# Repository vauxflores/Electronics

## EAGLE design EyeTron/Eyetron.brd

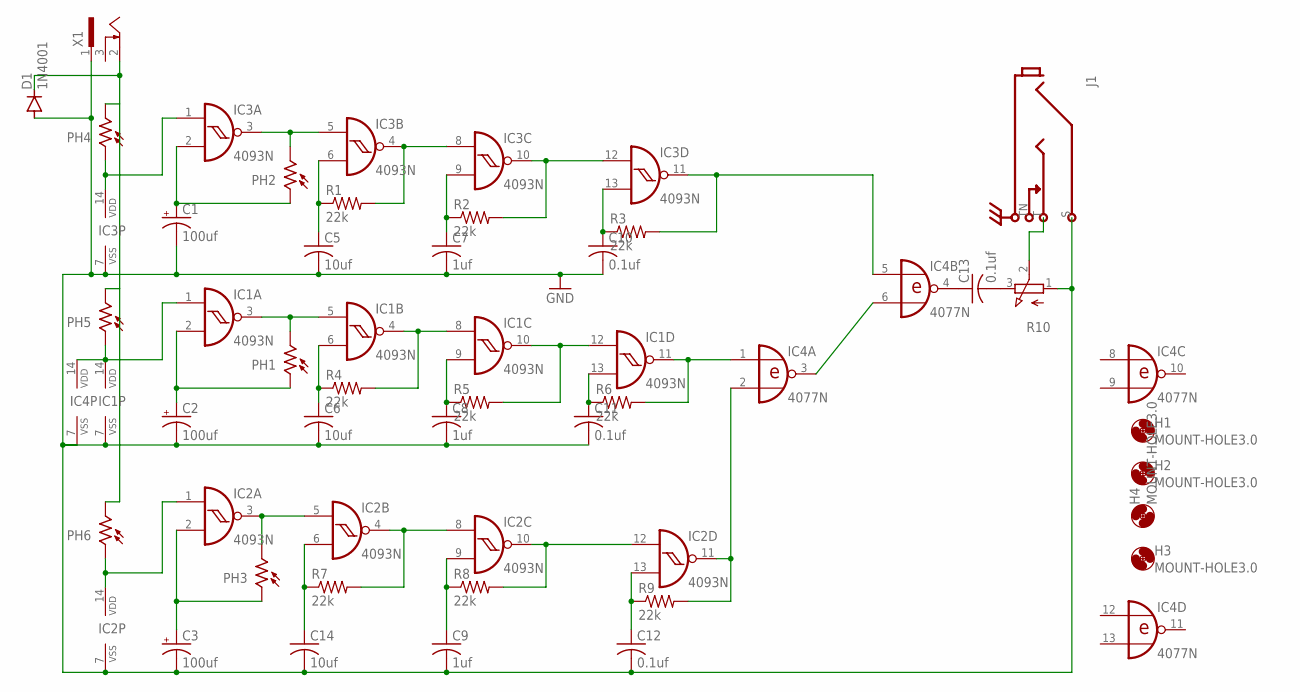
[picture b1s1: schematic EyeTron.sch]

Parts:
C1, C2, C3: 100uf; E2,5-6E
C5, C6, C14: 10uf; C050-025X075
C7, C8, C9: 1uf; C050-025X075
C10, C11, C12, C13: 0.1uf; C050-025X075
D1: 1N4001; DO41-10
H1, H2, H3, H4: MOUNT-HOLE3.0; 3,0
IC1, IC2, IC3: 4093N; DIL14
IC4: 4077N; DIL14
J1: MONOSW1GND; NEUTRIK-NRJ4HM-1
PH1, PH2, PH3, PH4, PH5, PH6: VT90N1; VT900
R1, R2, R3, R4, R5, R6, R7, R8, R9: 22k; 0207/7
R10: EVUF2L; EVUFXL
X1: SCD-014A; SCD-014-A

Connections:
GND: C1.-, C2.-, C3.-, C5.2, C6.2, C7.2, C8.2, C9.2, C10.2, C11.2, C12.2, C14.2, D1.A, IC1.7 (VSS), IC2.7 (VSS), IC3.7 (VSS), IC4.7 (VSS), J1.S, R10.1 (A), X1.1
unnamed: IC1.11 (O), IC4.1 (I0), R6.2
unnamed: IC1.10 (O), IC1.12 (I0), R5.2
unnamed: IC1.4 (O), IC1.8 (I0), R4.2
unnamed: IC1.3 (O), IC1.5 (I0), PH1.2
unnamed: IC2.3 (O), IC2.5 (I0), PH3.2
unnamed: IC2.4 (O), IC2.8 (I0), R7.2
unnamed: IC2.10 (O), IC2.12 (I0), R8.2
unnamed: IC2.11 (O), IC4.2 (I1), R9.2
unnamed: IC4.3 (O), IC4.6 (I1)
unnamed: IC3.3 (O), IC3.5 (I0), PH2.2
unnamed: IC3.4 (O), IC3.8 (I0), R1.2
unnamed: IC3.10 (O), IC3.12 (I0), R2.2
unnamed: IC3.11 (O), IC4.5 (I0), R3.2
unnamed: C1.+, IC3.2 (I1), PH2.1
unnamed: C2.+, IC1.2 (I1), PH1.1
unnamed: C3.+, IC2.2 (I1), PH3.1
unnamed: C5.1, IC3.6 (I1), R1.1
unnamed: C7.1, IC3.9 (I1), R2.1
unnamed: IC3.1 (I0), IC3.14 (VDD), PH4.1
unnamed: C10.1, IC3.13 (I1), R3.1
unnamed: IC1.1 (I0), IC1.14 (VDD), IC4.14 (VDD), PH5.1
unnamed: C6.1, IC1.6 (I1), R4.1
unnamed: C8.1, IC1.9 (I1), R5.1
unnamed: C11.1, IC1.13 (I1), R6.1
unnamed: C14.1, IC2.6 (I1), R7.1
unnamed: C9.1, IC2.9 (I1), R8.1
unnamed: C12.1, IC2.13 (I1), R9.1
unnamed: IC2.1 (I0), IC2.14 (VDD), PH6.1
unnamed: D1.C, PH4.2, PH5.2, PH6.2, X1.2
unnamed: C13.1, IC4.4 (O)
unnamed: C13.2, R10.3 (E)
unnamed: J1.T, R10.2 (S)

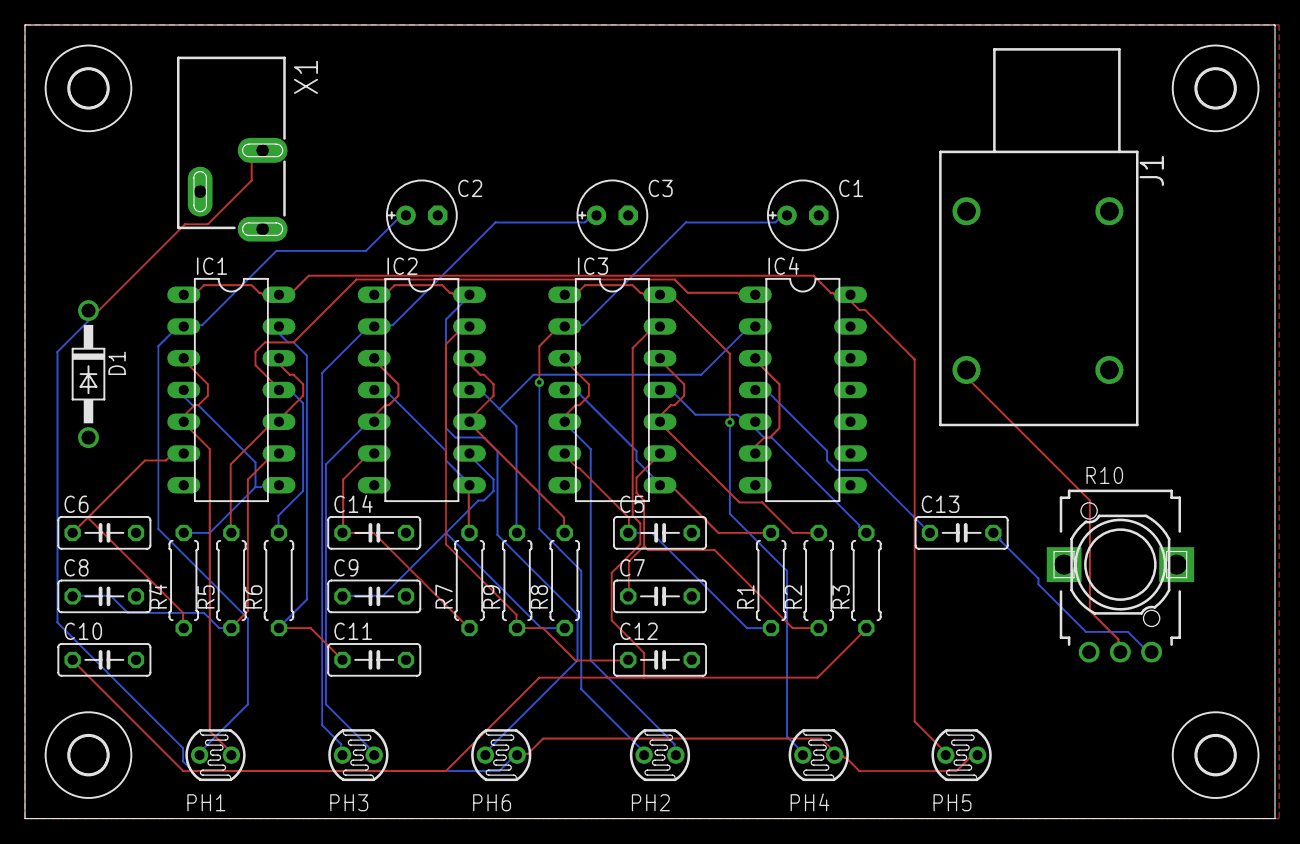
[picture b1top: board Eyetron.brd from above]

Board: 2 copper layers, 100.0 x 63.5 mm, 40 parts (0 on the bottom side), 33 nets.

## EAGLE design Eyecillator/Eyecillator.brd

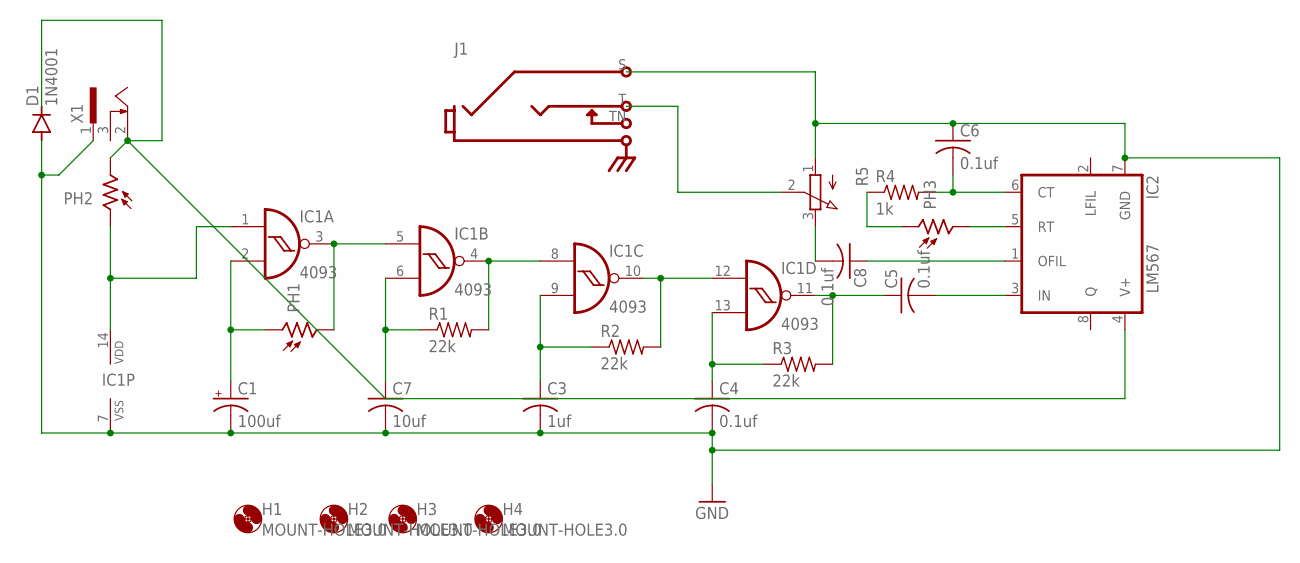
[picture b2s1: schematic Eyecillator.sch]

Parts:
C1: 100uf; E2,5-6E
C3: 1uf; C050-025X075
C4, C5, C6, C8: 0.1uf; C050-025X075
C7: 10uf; C050-025X075
D1: 1N4001; DO41-10
H1, H2, H3, H4: MOUNT-HOLE3.0; 3,0
IC1: 4093; DIL14
IC2: LM567; DIL08
J1: MONOSW1GND; NEUTRIK-NRJ4HM-1
PH1, PH2, PH3: VT90N1; VT900
R1, R2, R3: 22k; 0207/7
R4: 1k; 0207/7
R5: EVUF2L; EVUFXL
X1: SCD-014A; SCD-014-A

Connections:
GND: C1.-, C3.2, C4.2, C6.1, C7.2, D1.A, IC1.7 (VSS), IC2.7 (GND), J1.S, R5.1 (A), X1.1
unnamed: IC1.3 (O), IC1.5 (I0), PH1.2
unnamed: IC1.4 (O), IC1.8 (I0), R1.2
unnamed: IC1.10 (O), IC1.12 (I0), R2.2
unnamed: C1.+, IC1.2 (I1), PH1.1
unnamed: C7.1, IC1.6 (I1), R1.1
unnamed: C3.1, IC1.9 (I1), R2.1
unnamed: C4.1, IC1.13 (I1), R3.1
unnamed: C5.1, IC1.11 (O), R3.2
unnamed: IC1.1 (I0), IC1.14 (VDD), PH2.1
unnamed: C5.2, IC2.3 (IN)
unnamed: C6.2, IC2.6 (CT), R4.2
unnamed: IC2.5 (RT), PH3.2
unnamed: PH3.1, R4.1
unnamed: C8.1, IC2.1 (OFIL)
unnamed: C8.2, R5.3 (E)
unnamed: D1.C, IC2.4 (V+), PH2.2, X1.2
unnamed: J1.T, R5.2 (S)

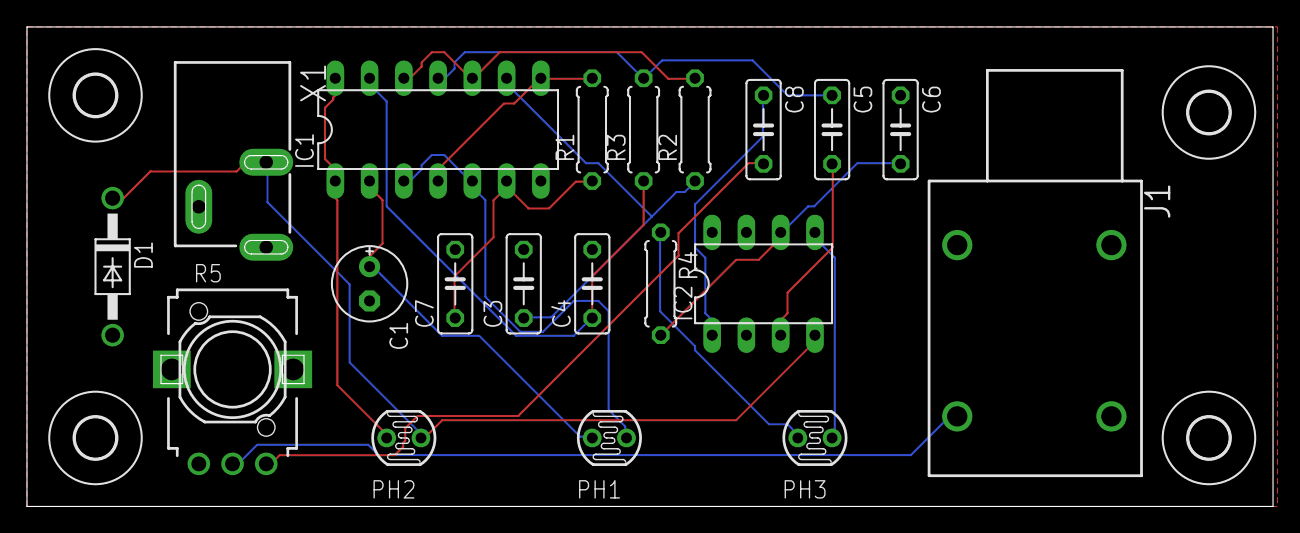
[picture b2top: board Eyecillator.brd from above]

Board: 2 copper layers, 92.4 x 35.5 mm, 24 parts (0 on the bottom side), 18 nets.

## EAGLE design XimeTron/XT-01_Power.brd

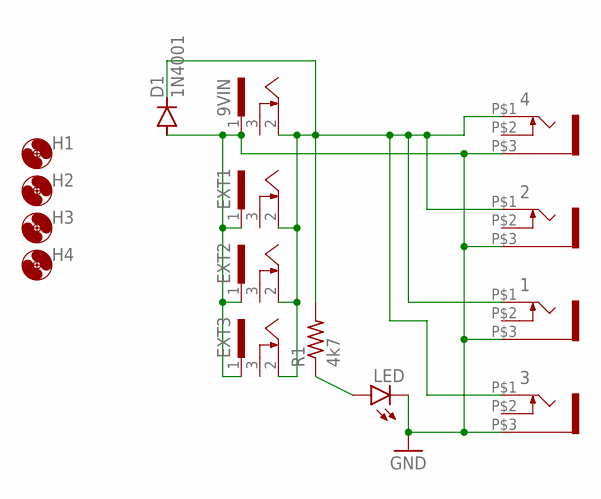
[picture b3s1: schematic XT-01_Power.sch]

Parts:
1, 2, 3, 4: WQP-PJ301M-12_JACK
9VIN: SCD-014A; SCD-014-A
D1: 1N4001; DO41-10
EXT1, EXT2, EXT3: SCD-014A; SCD-014-A
H1, H2, H3, H4: MOUNT-HOLE3.0; 3,0
LED: LED3MM
R1: 4k7; 0207/7

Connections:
GND: 1.P$3 (1), 2.P$3 (1), 3.P$3 (1), 4.P$3 (1), 9VIN.1, D1.A, EXT1.1, EXT2.1, EXT3.1, LED.K (C)
unnamed: LED.A, R1.1
unnamed: 1.P$1 (2), 2.P$1 (2), 3.P$1 (2), 4.P$1 (2), 9VIN.2, D1.C, EXT1.2, EXT2.2, EXT3.2, R1.2

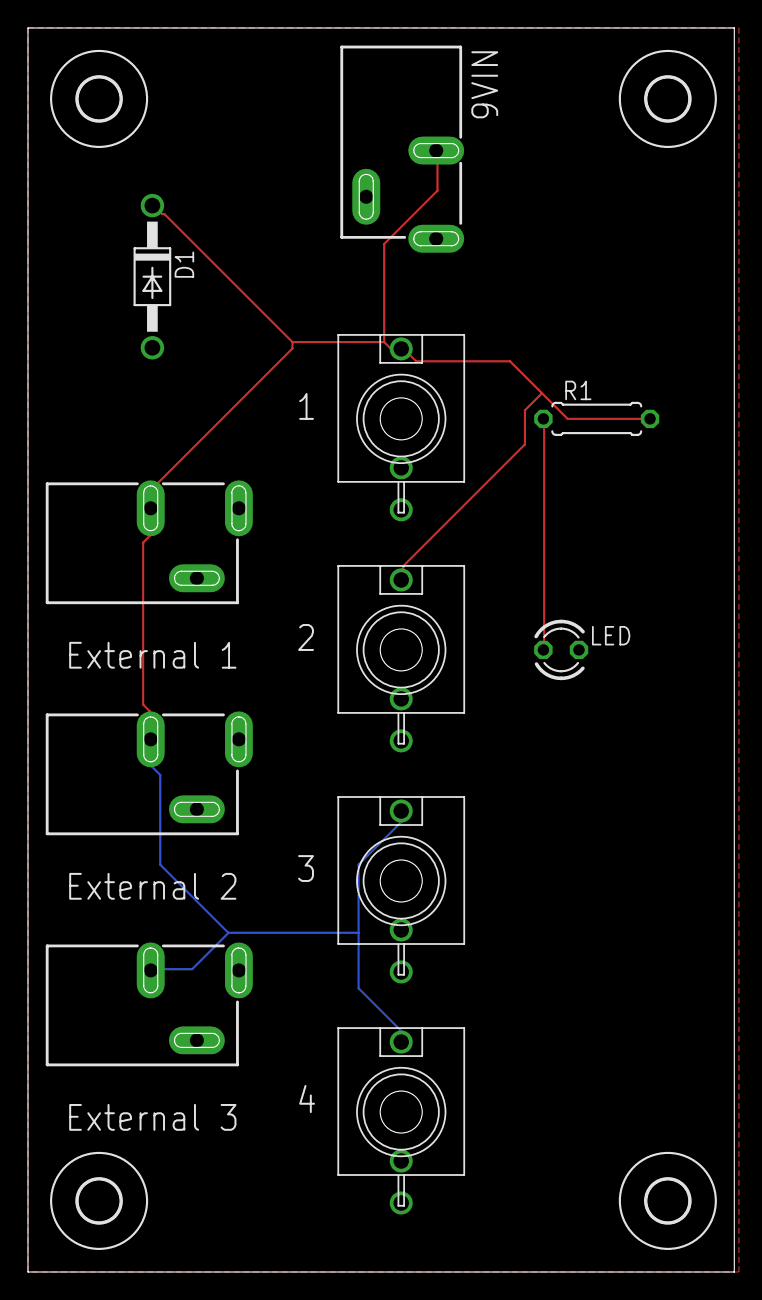
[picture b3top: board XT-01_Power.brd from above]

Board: 2 copper layers, 50.5 x 88.9 mm, 15 parts (0 on the bottom side), 3 nets.

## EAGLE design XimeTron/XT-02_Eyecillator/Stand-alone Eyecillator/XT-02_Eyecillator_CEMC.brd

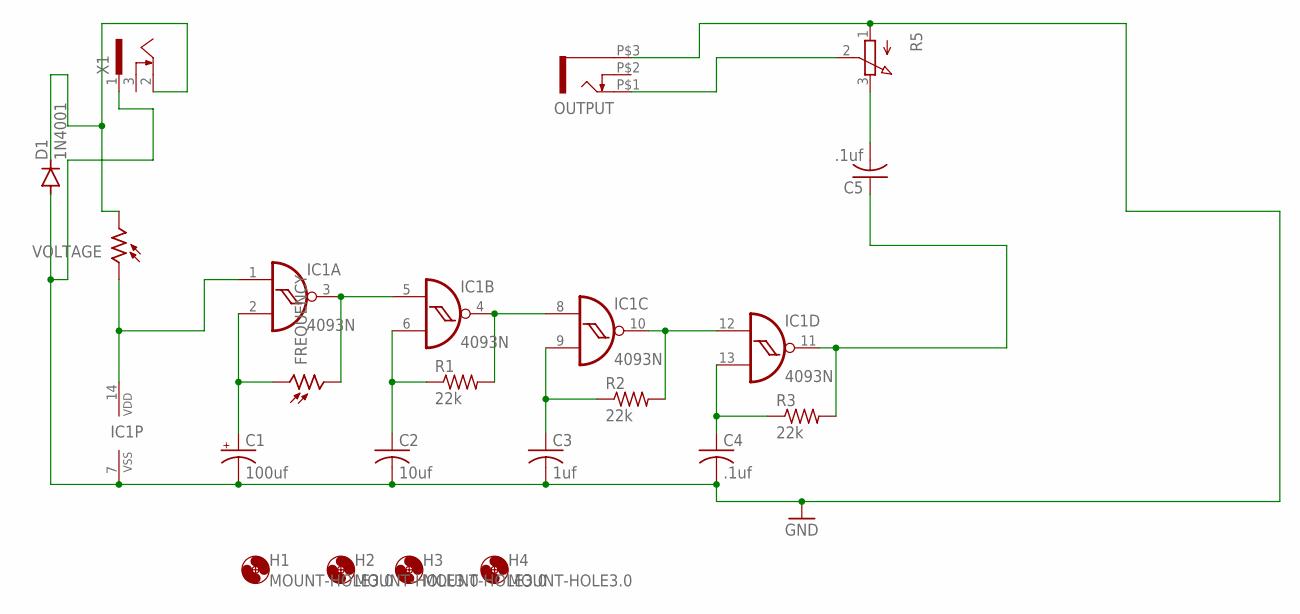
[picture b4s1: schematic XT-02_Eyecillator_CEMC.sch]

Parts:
C1: 100uf; E2,5-6E
C2: 10uf; C050-025X075
C3: 1uf; C050-025X075
C4, C5: .1uf; C050-025X075
D1: 1N4001; DO41-10
FREQUENCY: VT90N1; VT900
H1, H2, H3, H4: MOUNT-HOLE3.0; 3,0
IC1: 4093N; DIL14
OUTPUT: WQP-PJ301M-12_JACK
R1, R2, R3: 22k; 0207/7
R5: EVUF2L; EVUFXL
VOLTAGE: VT90N1; VT900
X1: SCD-014A; SCD-014-A

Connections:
GND: C1.-, C2.2, C3.2, C4.2, D1.A, IC1.7 (VSS), OUTPUT.P$3 (1), R5.1 (A), X1.1
unnamed: FREQUENCY.2, IC1.3 (O), IC1.5 (I0)
unnamed: IC1.4 (O), IC1.8 (I0), R1.2
unnamed: IC1.10 (O), IC1.12 (I0), R2.2
unnamed: C1.+, FREQUENCY.1, IC1.2 (I1)
unnamed: C2.1, IC1.6 (I1), R1.1
unnamed: C3.1, IC1.9 (I1), R2.1
unnamed: C4.1, IC1.13 (I1), R3.1
unnamed: C5.2, R5.3 (E)
unnamed: IC1.1 (I0), IC1.14 (VDD), VOLTAGE.1
unnamed: C5.1, IC1.11 (O), R3.2
unnamed: OUTPUT.P$1 (2), R5.2 (S)
unnamed: D1.C, VOLTAGE.2, X1.2

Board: 2 copper layers, 19 parts (0 on the bottom side), 13 nets, no tracks yet.

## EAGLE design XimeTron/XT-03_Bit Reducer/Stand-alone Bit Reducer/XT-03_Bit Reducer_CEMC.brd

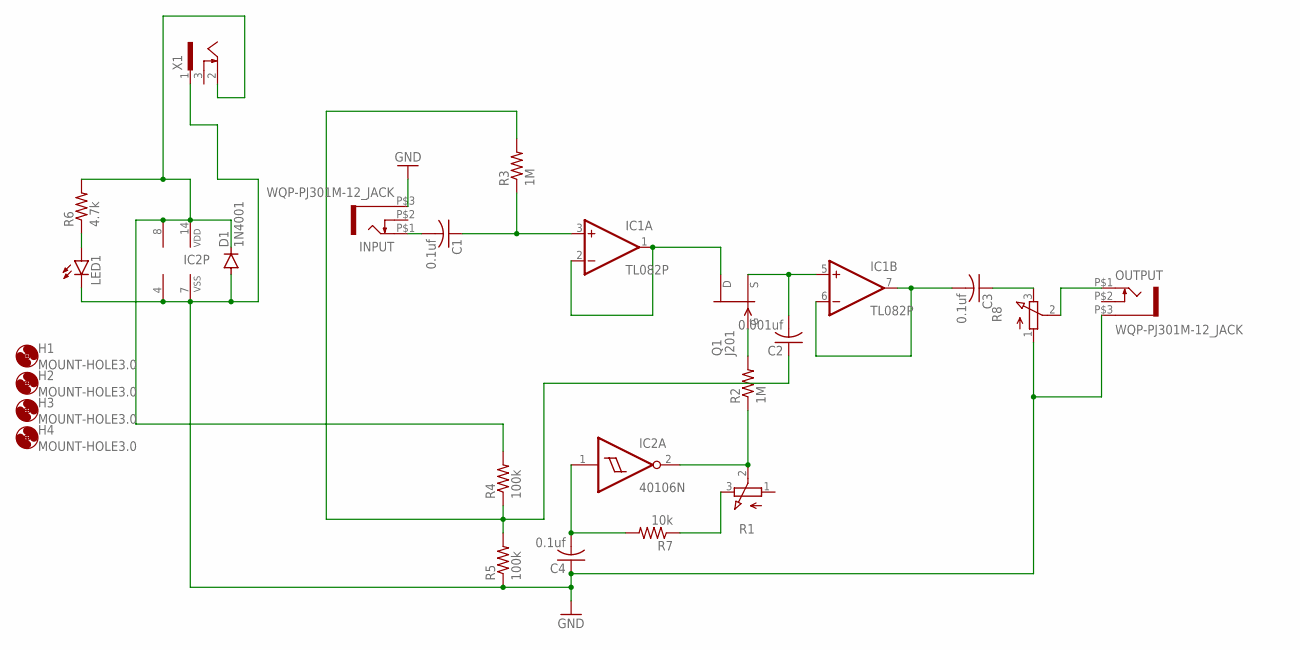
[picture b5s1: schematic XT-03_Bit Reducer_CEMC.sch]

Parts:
C1, C3, C4: 0.1uf; C050-025X075
C2: 0.001uf; C050-025X075
D1: 1N4001; DO41-10
H1, H2, H3, H4: MOUNT-HOLE3.0; 3,0
IC1: TL082P; DIL08
IC2: 40106N; DIL14
INPUT: WQP-PJ301M-12_JACK
LED1: LED3MM
OUTPUT: WQP-PJ301M-12_JACK
Q1: J201; TO92
R1, R8: EVUF2L; EVUFXL
R2, R3: 1M; 0207/7
R4, R5: 100k; 0207/7
R6: 4.7k; 0207/7
R7: 10k; 0207/7
X1: SCD-014A; SCD-014-A

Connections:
GND: C4.1, D1.A, IC1.4 (V-), IC2.7 (VSS), INPUT.P$3 (1), LED1.K (C), OUTPUT.P$3 (1), R5.1, R8.1 (A), X1.1
unnamed: Q1.1 (G), R2.2
unnamed: IC1.1 (OUT), IC1.2 (-IN), Q1.3 (D)
unnamed: C1.1, IC1.3 (+IN), R3.1
unnamed: C2.2, IC1.5 (+IN), Q1.2 (S)
unnamed: C3.2, IC1.6 (-IN), IC1.7 (OUT)
unnamed: C1.2, INPUT.P$1 (2)
unnamed: C2.1, R3.2, R4.1, R5.2
unnamed: C3.1, R8.3 (E)
unnamed: LED1.A, R6.1
unnamed: IC2.2 (O), R1.2 (S), R2.1
unnamed: R1.3 (E), R7.1
unnamed: OUTPUT.P$1 (2), R8.2 (S)
unnamed: C4.2, IC2.1 (I), R7.2
unnamed: D1.C, IC1.8 (V+), IC2.14 (VDD), R4.2, R6.2, X1.2

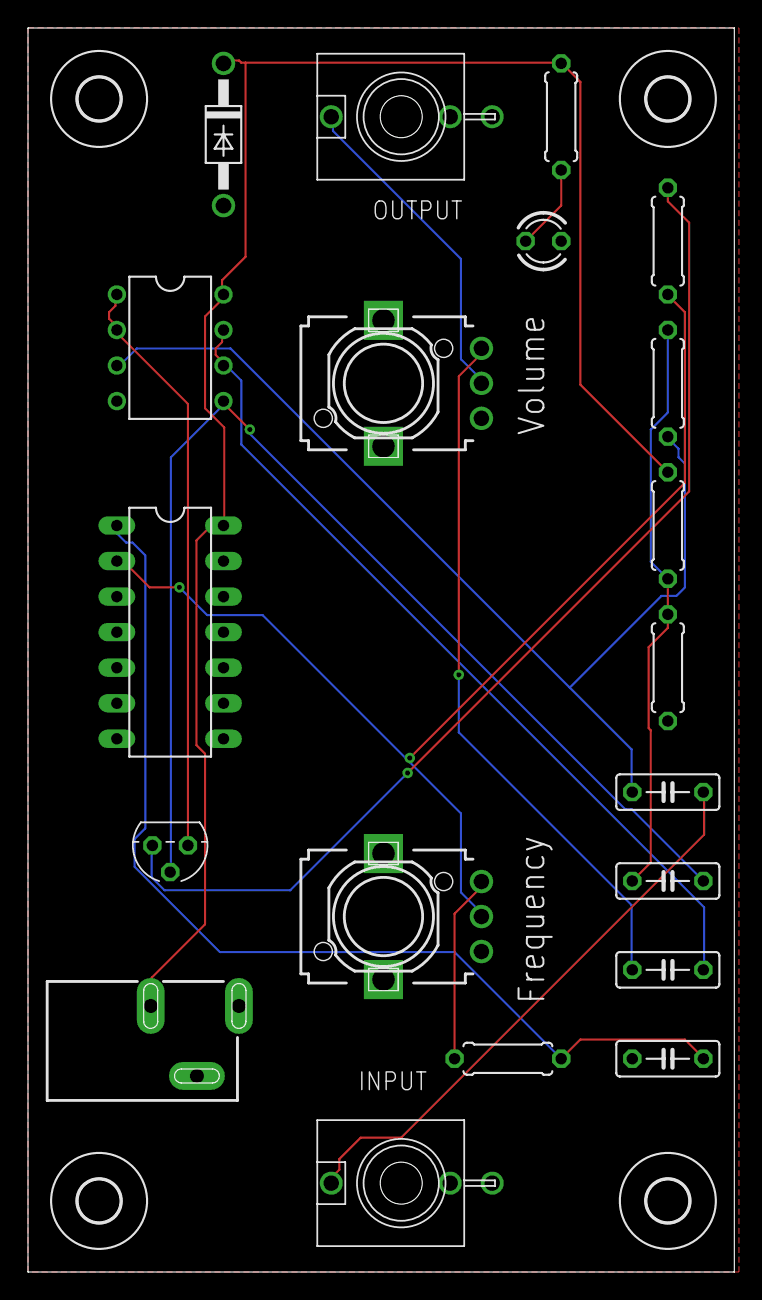
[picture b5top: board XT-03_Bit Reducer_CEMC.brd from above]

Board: 2 copper layers, 50.5 x 88.9 mm, 24 parts (0 on the bottom side), 15 nets.
